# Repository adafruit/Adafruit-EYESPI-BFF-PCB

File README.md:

## Adafruit EYESPI BFF for QT Py or Xiao - 18 Pin FPC Connector PCB

<a href="http://www.adafruit.com/products/5772"><br/>
Click here to purchase one from the Adafruit shop</a>

PCB files for the Adafruit EYESPI BFF for QT Py or Xiao - 18 Pin FPC Connector. 

Format is EagleCAD schematic and board layout
* https://www.adafruit.com/product/5772

### Description

Our QT Py boards are a great way to make very small microcontroller projects that pack a ton of power - and now we have a way for you to add a small, colorful, and bright display to any project.

Our most recent display breakouts have come with a new feature: an 18-pin "EYE SPI" standard FPC connector with flip-top connector. This is intended to be a sort-of "STEMMA QT for displays" - a way to quickly connect and extend display wiring that uses a lot of SPI pins. In this case we need a lot of SPI pins, and we want to be able to use long distances, so we go with an 18-pin 0.5mm pitch FPC.

With such a slim and flexible cable, its a perfect matching for our QT Py boards to make extra smol microcontroller boards with big bold colorful displays or power-sipping E-Ink. 

Don't forget you'll also want an 18-pin EYESPI FPC cable. And of course one of our EYESPI displays too - look for the EYESPI logo on the back to know you've got one that can clip in.

* MOSI/MISO/SCK SPI pins are connected to the default SPI port on the QT Py
* SDA/SCL I2C pins are connected to the I2C port on the QT Py headers - some boards have a separate QT Py I2C port so keep in mind they may be separate busses.
* TFT CS on TX pin - but can be re-configured/disabled by cutting a solder jumper.
* TFT DC on RX pin - but can be re-configured/disabled by cutting a solder jumper.

We also have 'sometimes used' pins that can be re-configured/disabled by cutting a solder jumper

* IRQ on A0 pin - Many of our displays don't use the IRQ pin unless there's a touchscreen.
* Touch CS on A1 pin - Many of our displays don't have a touchscreen.
* Memory CS on A2 pin - Only our E-Ink displays have a separate memory SRAM chip, which you may be able to skip using on most QT Py's.
* SD Card CS on A3 pin - Or use for whatever you like if you aren't using the SD Card socket on of our display breakouts.

There's also two through-hole solder pads for extra pins that are often considered optional and we didn't have any more IO to spare. If you aren't using any of the 4 pins above or the I2C port, you could wire these two pins with jumper wires as you desire.

* Backlight control - this is default on for most of our displays, or unused on E-Ink,
* Display reset -  this is default on for most of our displays. Sometimes its used for low-power on E-Ink.

We include some header that you can solder to your QT Py. You can also pick up an Itsy Bitsy short female header kit to make it removable but compact, you'll just need to trim down the headers to 7 pins long.

Comes as an assembled and tested PCB
For any QT Py or Xiao boards
QT Py, display and EYESPI cable are not included.

### License

Adafruit invests time and resources providing this open source design, please support Adafruit and open-source hardware by purchasing products from [Adafruit](https://www.adafruit.com)!

Designed by Limor Fried/Ladyada for Adafruit Industries.

Creative Commons Attribution/Share-Alike, all text above must be included in any redistribution. 
See license.txt for additional details.

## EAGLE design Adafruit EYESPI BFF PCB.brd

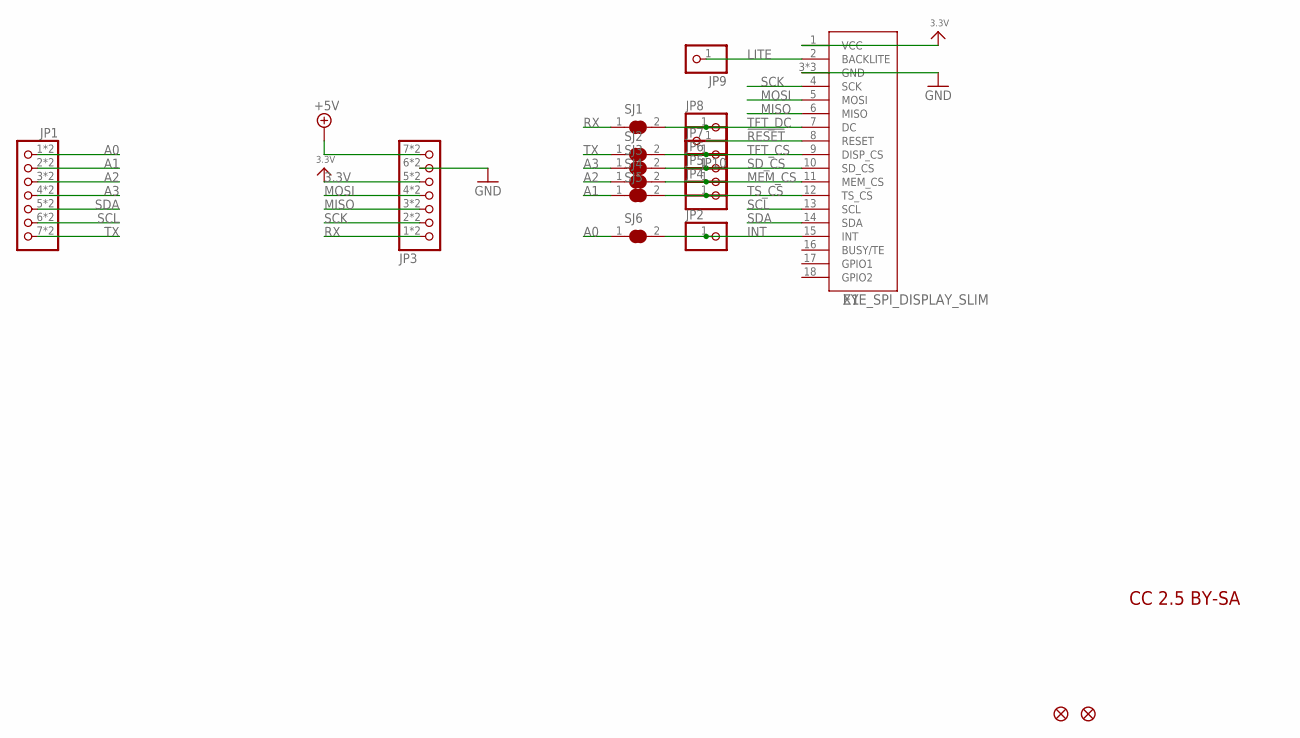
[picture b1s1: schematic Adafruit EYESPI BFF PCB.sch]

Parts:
JP1, JP3: HEADER-1X7_CASTEL; 1X07_CASTEL
JP2, JP4, JP5, JP6, JP7, JP8, JP9, JP10: HEADER-1X12MM; 1X01_2MM
SJ1, SJ2, SJ3, SJ4, SJ5, SJ6: SOLDERJUMPER_CLOSED; SOLDERJUMPER_CLOSEDWIRE
U$6, U$8: FIDUCIAL_1MM
X1: EYE_SPI_DISPLAY_SLIM

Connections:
3.3V: JP3.5, JP3.5C (5), X1.1 (VCC)
!RESET: JP10.1, X1.8 (RESET)
+5V: JP3.7, JP3.7C (7)
A0: JP1.1, JP1.1C (1), SJ6.1
A1: JP1.2, JP1.2C (2), SJ5.1
A2: JP1.3, JP1.3C (3), SJ4.1
A3: JP1.4, JP1.4C (4), SJ3.1
GND: JP3.6, JP3.6C (6), X1.3 (GND), X1.SUPPORT1 (GND), X1.SUPPORT2 (GND)
INT: JP2.1, SJ6.2, X1.15 (INT)
LITE: JP9.1, X1.2 (BACKLITE)
MEM_CS: JP5.1, SJ4.2, X1.11 (MEM_CS)
MISO: JP3.3, JP3.3C (3), X1.6 (MISO)
MOSI: JP3.4, JP3.4C (4), X1.5 (MOSI)
RX: JP3.1, JP3.1C (1), SJ1.1
SCK: JP3.2, JP3.2C (2), X1.4 (SCK)
SCL: JP1.6, JP1.6C (6), X1.13 (SCL)
SDA: JP1.5, JP1.5C (5), X1.14 (SDA)
SD_CS: JP6.1, SJ3.2, X1.10 (SD_CS)
TFT_CS: JP7.1, SJ2.2, X1.9 (DISP_CS)
TFT_DC: JP8.1, SJ1.2, X1.7 (DC)
TS_CS: JP4.1, SJ5.2, X1.12 (TS_CS)
TX: JP1.7, JP1.7C (7), SJ2.1

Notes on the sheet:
CC 2.5 BY-SA

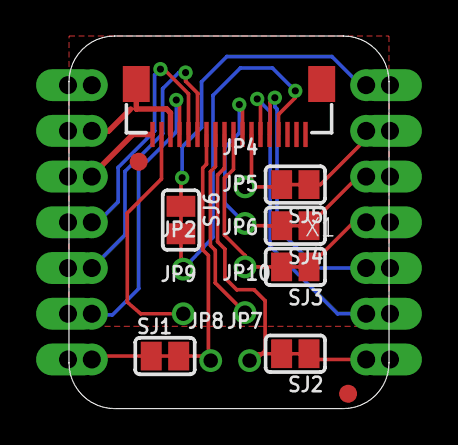
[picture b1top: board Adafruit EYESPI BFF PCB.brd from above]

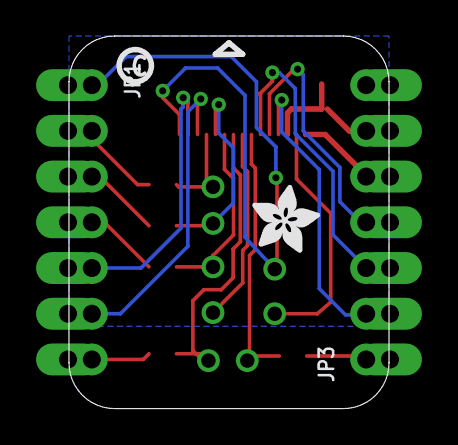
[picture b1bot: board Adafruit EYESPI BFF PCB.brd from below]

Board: 2 copper layers, 17.8 x 20.7 mm, 54 parts (14 on the bottom side), 22 nets.

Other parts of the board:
PLABEL1: PLABEL1
PLABEL2: PLABEL2
PLABEL3: PLABEL3
PLABEL4: PLABEL4
PLABEL5: PLABEL5
PLABEL6: PLABEL6
PLABEL7: PLABEL7
PLABEL8: PLABEL8
PLABEL9: PLABEL9
PLABEL10: PLABEL10
PLABEL11: PLABEL11
PLABEL12: PLABEL12
PLABEL13: PLABEL13
PLABEL14: PLABEL14
PLABEL19: PLABEL19
PLABEL20: PLABEL20
PLABEL21: PLABEL21
PLABEL22: PLABEL22
PLABEL23: PLABEL23
PLABEL24: PLABEL24
PLABEL25: PLABEL25
PLABEL26: PLABEL26
PLABEL27: PLABEL27
PLABEL28: PLABEL28
PLABEL29: PLABEL29
PLABEL30: PLABEL30
PLABEL31: PLABEL31
PLABEL32: PLABEL32
PLABEL33: PLABEL33
PLABEL34: PLABEL34
PLABEL35: PLABEL35
PLABEL36: PLABEL36
PLABEL37: PLABEL37
U$2: ADAFRUIT_3.5MM
U$3: PCBFEAT-REV-040

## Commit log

2023-06-26 adding cookiecutter output

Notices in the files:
parts and their libraries:
microbuilder: This work is placed in the public domain, and may be freely used for commercial and non-commercial work with the following conditions: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
